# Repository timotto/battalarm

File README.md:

# Battery Alarm

A device to alert you in case you forget to plug in the starter-battery charger into your vehicle.

## Why

Usually a vehicle's starter battery is charged when the engine is running. 
But some utility vehicles contain many on-board electronics and accessory chargers,
draining the starter-battery when the vehicle sits idle for some time. 
In some cases just a weekend is enough.

## How does it work

Battery Alarm consists of two devices:
1. the alarm adapter to be plugged into the vehicle's cigarette lighter port  
2. a radio beacon to mount in the garage

The alarm adapter monitors the vehicle's starter-battery voltage. 
It will sound an audible alarm when the vehicle is close to the garage radio beacon, 
the starter-battery's voltage is below charging level, and some time has passed.

## How is it made

The firmware is written using Arduino and targets the ESP32 controller.

The alarm adapter has a small custom PCB to connect a voltage divider, a 5V power supply, and a buzzer to the ESP32.

The radio beacon is just a plain ESP32 board with no additional electronics but a wall plug to provide power.

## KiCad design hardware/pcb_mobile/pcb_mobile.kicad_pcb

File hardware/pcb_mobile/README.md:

# Battery Alarm Mobile Device PCB

This is the PCB used by the alarm devices mounted in the vehicle.

It is designed to be etched at home or milled with a cheap CNC router.

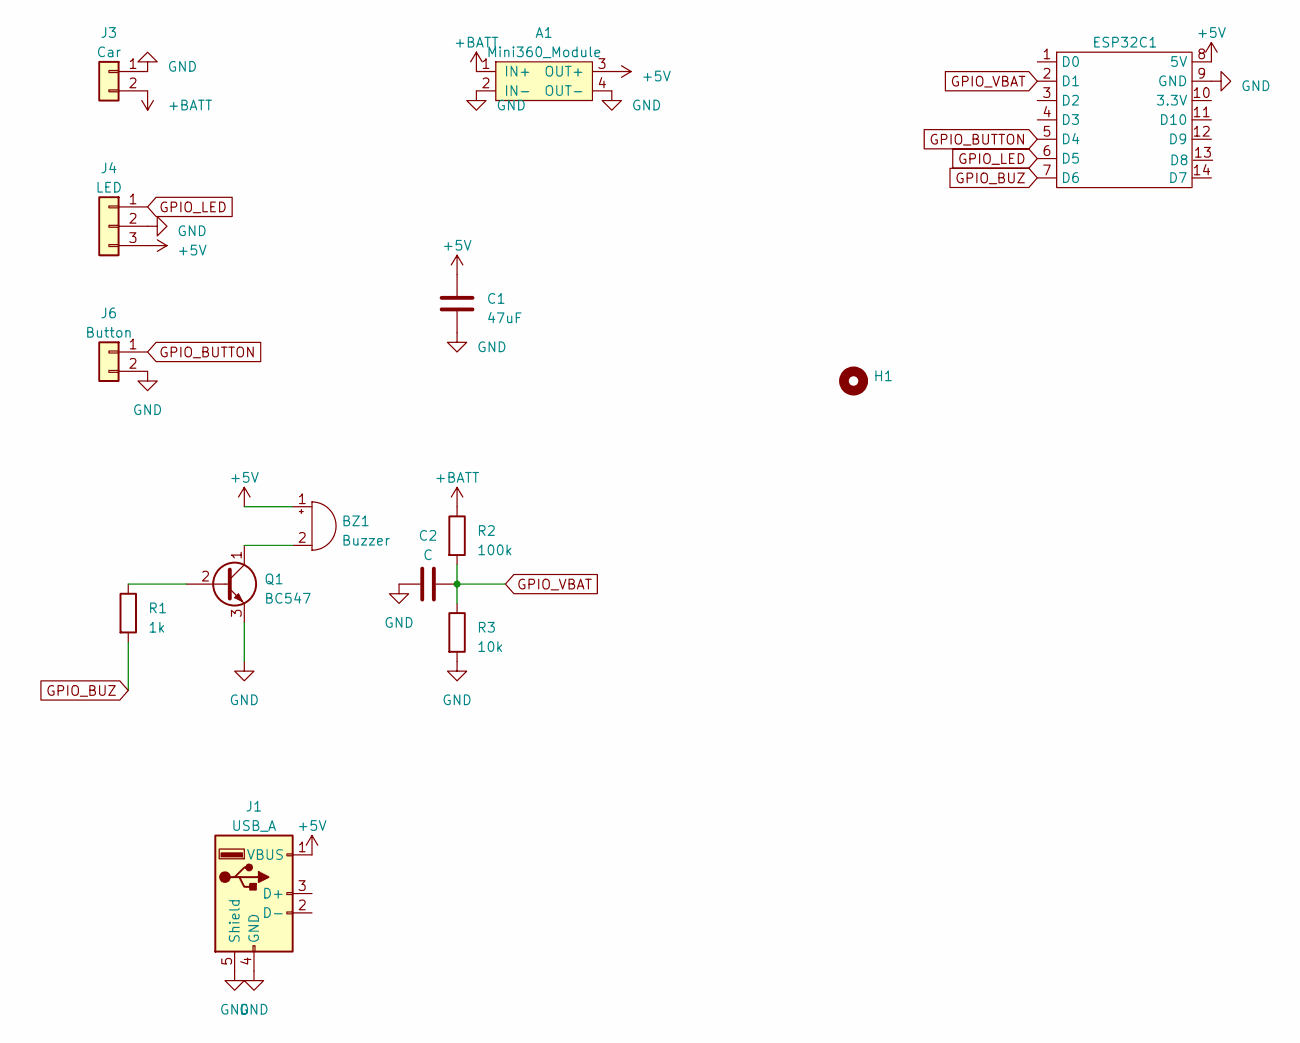
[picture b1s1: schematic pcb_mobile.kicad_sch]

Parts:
A1: Mini360_Module
BZ1: Buzzer; Buzzer_12x9.5RM7.6
C1: 47uF; CP_Radial_D5.0mm_P2.50mm
C2: C; C_Disc_D3.0mm_W2.0mm_P2.50mm
ESP32C1: XIAO_ESP32C3_1
H1: MountingHole_3.2mm_M3
J1: USB_A; USB_A_Molex_67643_Horizontal
J3: Car; PinHeader_1x02_P2.54mm_Vertical
J4: LED; PinHeader_1x03_P2.54mm_Vertical
J6: Button; PinHeader_1x02_P2.54mm_Vertical
Q1: BC547; TO-92_Wide
R1: 1k; R_Axial_DIN0204_L3.6mm_D1.6mm_P2.54mm_Vertical
R2: 100k; R_Axial_DIN0207_L6.3mm_D2.5mm_P7.62mm_Horizontal
R3: 10k; R_Axial_DIN0207_L6.3mm_D2.5mm_P7.62mm_Horizontal

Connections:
+5V: A1.3 (OUT+), BZ1.1 (-), C1.1, ESP32C1.8 (5V), J1.1 (VBUS), J4.3
+BATT: A1.1 (IN+), J3.2, R2.1
GND: A1.2 (IN-), A1.4 (OUT-), C1.2, C2.1, ESP32C1.9 (GND), J1.4 (GND), J1.5 (Shield), J3.1, J4.2, J6.2, Q1.3 (E), R3.2
GPIO_BUTTON: ESP32C1.5 (D4), J6.1
GPIO_BUZ: ESP32C1.7 (D6), R1.2
GPIO_LED: ESP32C1.6 (D5), J4.1
GPIO_VBAT: C2.2, ESP32C1.2 (D1), R2.2, R3.1
unnamed: BZ1.2 (+), Q1.1 (C)
unnamed: Q1.2 (B), R1.1

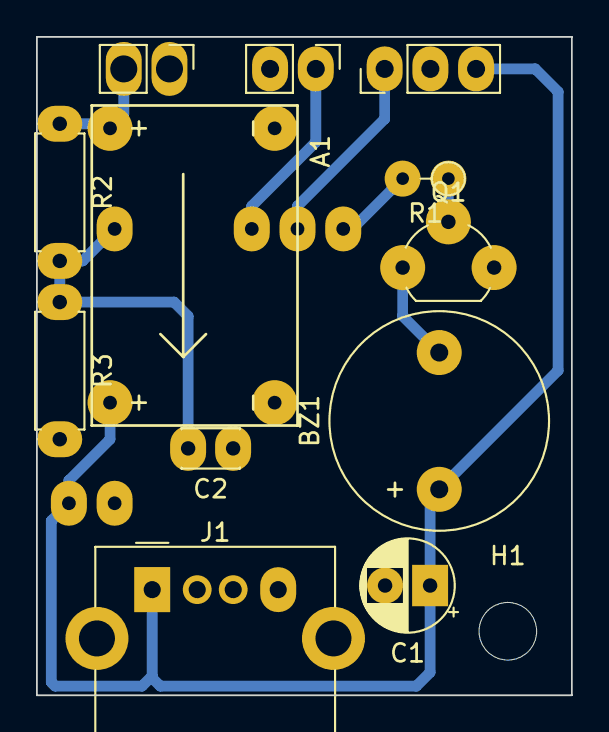
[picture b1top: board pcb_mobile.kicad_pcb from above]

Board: 2 copper layers, 29.7 x 36.6 mm, 14 parts (1 on the bottom side), 9 nets.

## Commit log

2024-05-15 📡 beacon firmware
2024-05-15 🚒 vehicle firmware
2024-05-15 🧼 refactoring
2024-05-15 🔎 more bt rssi results
2024-05-15 🖨️ status output
2024-05-15 🎛️ bt config & status interface
2024-05-15 🔘 toggle bt visibility with button
2024-05-15 🔑 require bt bonding
2024-05-15 🔊 configure buzzer alert level
2024-05-17 🐞 fix bug
2024-05-17 🧽 refactoring
2024-05-17 😴 report low rssi when not in range
2024-05-17 🍪 pin config for ESP32C3
2024-05-17 😇 remove ble pairing code
2024-05-17 📱 settings config app
2024-05-17 🫴 handle ble exceptions
2024-05-17 💄 nicer scan list experience
2024-05-17 💾 fix missing pref
2024-05-17 🔌 nicer connecting text
2024-05-17 💎 replace provider logic
2024-05-17 🚿 refactoring
2024-05-17 🖼️ app icon & name
2024-05-17 🙈 don't flicker "no bluetooth" when still checking
2024-05-18 🪧 show message on connection error
2024-05-18 🧢 indicate bluetooth activity
2024-05-18 💄 cosmetics
2024-05-18 🧴 cosmetics
2024-05-19 🔋 configure vbat fine tuning with app
2024-05-19 🧑‍🔬 hide rare config items in expert view
2024-05-19 📡 select beacon in app
2024-05-19 🤷 disable ibeacon so app can find the station
2024-05-19 🚦 switch led library
2024-05-20 🎁 add missing app assets
2024-05-20 🧑‍🦯 hide another expert setting
2024-05-20 ⚖️ show licenses in about app dialog
2024-05-20 🚀 setup fastlane for android
2024-05-20 🔧 fix android application id
2024-05-21 🖼️ new icon
2024-05-21 🤜 bump flutter to 3.22
2024-05-21 ✅ green checkmarks on status screen
2024-05-21 💡 make DeviceClient a singleton
2024-05-21 😊 apply current reading as config
2024-05-23 🔘 capacitive touch button is active high
2024-05-23 🤩 full-blown localized user manual with pictures and videos
2024-05-23 🔧 fix ci
2024-05-23 🚫 disable ng cli analytics
2024-05-23 🔨 fix chart
2024-05-23 🌎 build localized by default
2024-05-23 🥖 remove non-existing language
2024-05-23 🎢 app pipeline
2024-05-23 🔧 fix pipeline
2024-05-23 😔 the app has no tests
2024-05-23 🔢 use matching app build image version
2024-05-23 🪛 fix android lane names
2024-05-23 🎯 improve ci triggers
2024-05-23 🤜 bump android publish image
2024-05-23 😇 really fix android track names
2024-05-23 🔧 fix publish android image repository name
2024-05-23 📰 use localized page title
2024-05-23 🧹 cleanup
2024-05-23 📷 add app screenshots to docs
2024-05-23 📝 more intro text
2024-05-23 😅 switch translations to arb format
2024-05-23 📺 re-position screenshots
2024-05-23 🌍 localize app
2024-05-23 🎓 promote to closed testing automatically
2024-05-23 🖼️ update docs favicon
2024-05-23 📖 fix missing app translations
2024-05-23 🤜 upgrade to angular 18
2024-05-23 🔦 highlight active navigation item
2024-05-23 🖼️ add icons to navigation items
2024-05-23 🎥 view transitions
2024-05-23 🤤 put 3d rendering of adapter into introduction
2024-05-23 🤩 material-3 theme, sort of
2024-05-23 🤕 work around early angular adoption suffering
2024-05-23 🪧 redirect to introduction on empty route
2024-05-23 ⏳ don't use permanent redirect
2024-05-23 👊 auto-bump app version on prod release
2024-05-24 🎼 re-format pipeline
2024-05-24 🧑‍🦯 add missing image alt text
2024-05-24 🥰 replace primeng with own image viewer
2024-05-24 🖼️ layout
2024-05-24 📔 re-order chapters
2024-05-24 🪛 fix full screen image on mobile
2024-05-24 🤳 fix screenshot layout on mobile
2024-05-24 💰 don't preload videos
2024-05-24 🎬 add missing video posters
2024-05-25 ⚡️ configure alternator voltage
2024-05-25 🩹 don't crash on missing ble characteristics
2024-05-25 🙅 refuse to edit non existing config properties
2024-05-25 🌍 add missing translation
2024-05-25 🎭 allow to fake voltage instead of charging state
2024-05-25 🧮 include alternator voltage threshold in charging state computation
2024-05-25 ⏎ add required line feed
2024-05-25 🎉 ble ota device implementation
2024-05-25 🎢 firmware pipeline
2024-05-25 🦋 larger connecting animation
2024-05-25 🤕 improve ota error handling
2024-05-26 🧹 proper ota state handling
2024-05-26 🐛 fix bugs
2024-05-26 🙉 disable scanning during ota
2024-05-26 🥰 ota from app
2024-05-26 🌎 ota localization
2024-05-26 🤖 support android app language
2024-05-26 🇺🇸 disable app language support
2024-05-26 🦿 upgrade agp
2024-05-26 🇩🇪 re-enable android app language
2024-05-26 🪮 smooth flash eta
2024-05-26 🇺🇸 add missing translation
2024-05-27 🎨 re-design ota dialog
2024-05-27 🏃 skip android closed testing
2024-05-27 ☎️ android app uses internet permission
2024-05-27 ✍️ log errors details
2024-05-28 🌎 translations
2024-05-28 🕰️ show download eta
2024-05-28 📦 store compressed firmware artifact
2024-05-28 🚮 don't store uncompressed firmware artifact
2024-05-28 🎁 flash compressed firmware update
2024-05-28 🐛 fix bug
2024-05-28 🦟 fix bug
2024-05-28 🎢 accelerate pipeline
2024-05-30 🎬 show animation while scanning
2024-05-30 🐜 fix microbug
2024-05-30 🔢 show adapter version in ota dialog
2024-05-30 🙈 hide build number from version from non developers
2024-05-30 🥰 nicer connect screen animation
2024-05-30 🚨 forward errors during flashing
2024-05-30 📽️ another animation
2024-05-30 ⏹️ no animation when there are no results
2024-05-30 🛵 respect engine running state
2024-05-30 ⏳ toggle bluetooth with ultra long press
2024-06-01 🛀 refactoring
2024-06-01 📝 update device bluetooth instruction
2024-06-01 🖼️ support landscape status page
2024-06-01 🫰 edit numeric values with slider
2024-08-14 🎢 set ota url in pipeline
2024-08-15 ⚡️ alarm device pcb
2024-08-15 📦 alarm device case
